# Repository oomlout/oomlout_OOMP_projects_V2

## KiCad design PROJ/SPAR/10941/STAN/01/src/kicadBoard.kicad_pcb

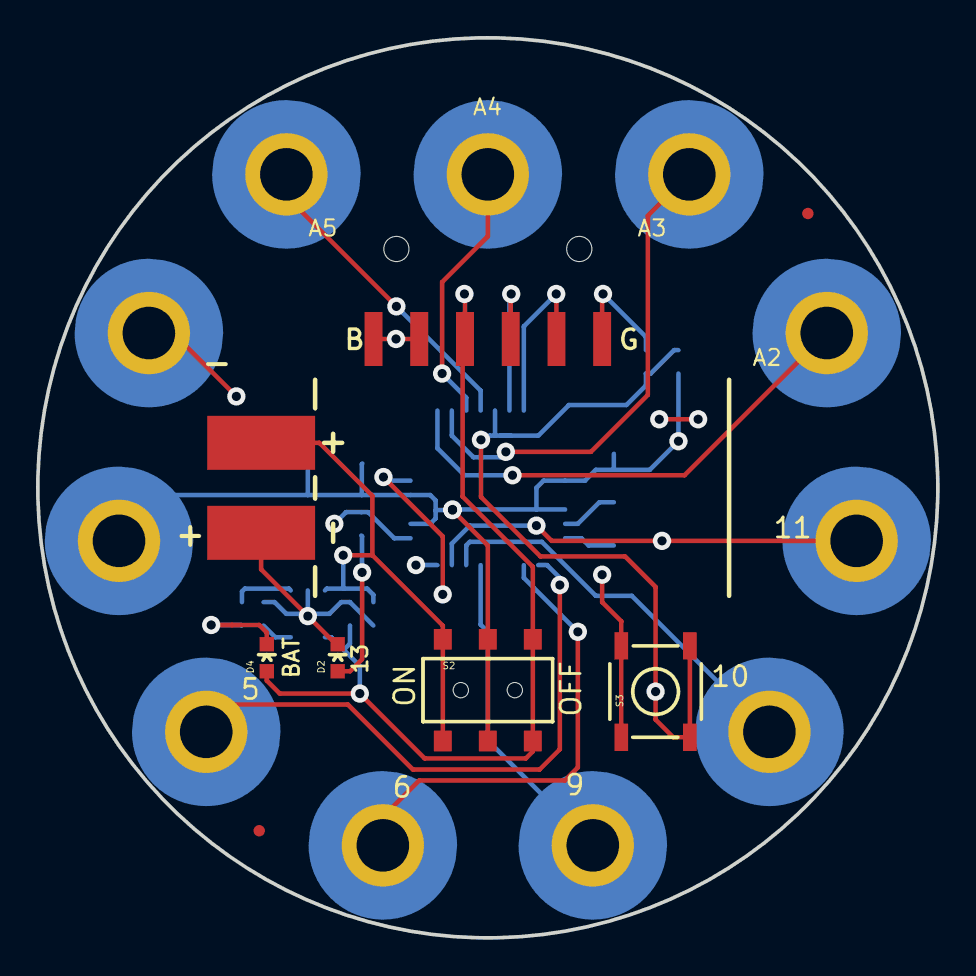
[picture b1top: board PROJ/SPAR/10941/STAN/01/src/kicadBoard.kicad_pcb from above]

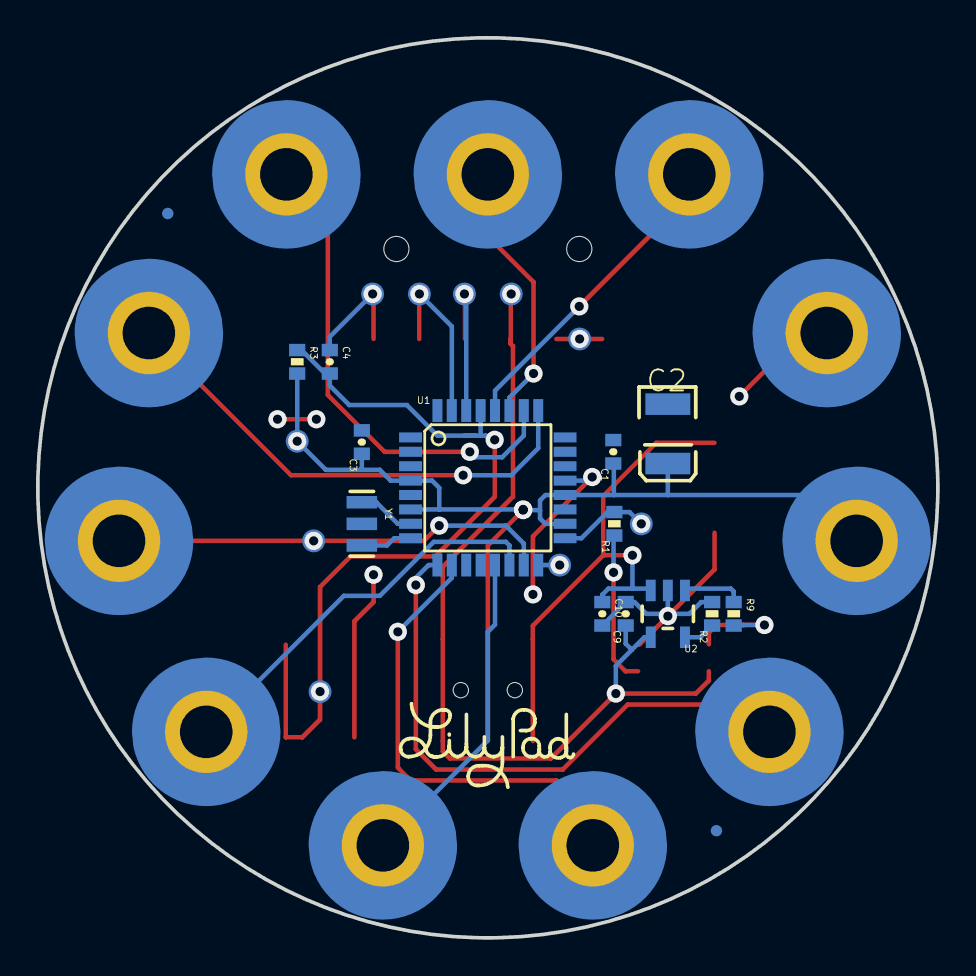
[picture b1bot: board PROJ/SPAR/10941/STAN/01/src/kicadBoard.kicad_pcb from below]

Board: 2 copper layers, 50.0 x 50.0 mm, 45 parts (37 on the bottom side), 25 nets.

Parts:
BAT1: LIPO-110-TABS
C1, C4: 0.1uF; 0402-CAP
C2: 47uF; EIA3528
C3: 1.0uF; 0402-CAP
C9, C10: 4.7uF; 0402-CAP
D2: Status; LED-0603
D4: Yellow; LED-0603
JP1, JP14, JP15, JP16: FIDUCIALUFIDUCIAL; MICRO-FIDUCIAL
JP2: 1X06-SMD
JP3, JP4, JP5, JP6, JP7, JP8, JP9, JP10, JP11, JP12, JP13: M01SNAP-FEMALE_LARGE; SNAP-FEMALE
PP-GND0: PAD.03X.05
PP-MISO0: PAD.03X.05
PP-MOSI0: PAD.03X.05
PP-RST0: PAD.03X.05
PP-SCK0: PAD.03X.05
PP-VCC0: PAD.03X.05
R1, R9: 330; 0402-RES
R2: 10k; 0402-RES
R3: 10K; 0402-RES
S2: On/Off; AYZ0202
S3: Reset; TACTILE_SWITCH_SMD
TP-DTR0: PAD.03X.05
TP-FTDI_VCC0: PAD.03X.05
TP-RX0: PAD.03X.05
TP-TX0: PAD.03X.05
U1: ATMEGA328; TQFP32-08
U2: MCP73831; SOT23-5
U$2: LOGO-LPLP; LOGO-LILYPAD
Y1: 8MHz; RESONATOR-SMD

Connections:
A2: JP3.1, U1.25
A3: JP4.1, U1.26
A4: JP5.1, U1.27
A5: JP6.1, U1.28
D5: JP7.1, U1.9
D6: JP8.1, U1.10
D9: JP9.1, U1.13
D10: JP10.1, U1.14
D11: JP11.1, PP-MOSI0.P$1, U1.15
D12: PP-MISO0.P$1, U1.16
D13: PP-SCK0.P$1, R1.2, U1.17
DTR: C4.1, JP2.1, TP-DTR0.P$1
FTDI_VCC: C9.1, D4.A, JP2.4, S2.3, S2.6, TP-FTDI_VCC0.P$1, U2.4
GND: BAT1.-, C1.2, C2.C, C3.2, C9.2, C10.2, D2.C, JP2.5, JP2.6, JP13.1, PP-GND0.P$1, R2.2, S3.1, U1.3, U1.5, U1.21, U2.2, Y1.2
unnamed: U1.7, Y1.1
unnamed: D2.A, R1.1
unnamed: U1.8, Y1.3
unnamed: D4.C, R9.2
PROG: R2.1, U2.5
RST: C4.2, PP-RST0.P$1, R3.1, S3.3, U1.29
RXI: JP2.3, TP-RX0.P$1, U1.30
STAT: R9.1, U2.1
TXO: JP2.2, TP-TX0.P$1, U1.31
VBATT: BAT1.+, C10.1, S2.1, S2.4, U2.3
VCC: C1.1, C2.A, C3.1, JP12.1, PP-VCC0.P$1, R3.2, S2.2, S2.5, U1.4, U1.6, U1.18, U1.20

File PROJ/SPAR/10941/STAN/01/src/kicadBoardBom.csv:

"Id";"Designator";"Package";"Quantity";"Designation";"Supplier and ref";
1;"JP2";"1X06-SMD";1;"";;;
2;"JP14,JP1,JP16,JP15";"MICRO-FIDUCIAL";4;"FIDUCIALUFIDUCIAL";;;
3;"D2";"LED-0603";1;"Status";;;
4;"BAT1";"LIPO-110-TABS";1;"";;;
5;"S3";"TACTILE_SWITCH_SMD";1;"Reset";;;
6;"D4";"LED-0603";1;"Yellow";;;
7;"S2";"AYZ0202";1;"On/Off";;;
8;"TP-DTR0,TP-FTDI_VCC0,TP-RX0,PP-RST0,PP-MOSI0,PP-SCK0,PP-VCC0,PP-GND0,PP-MISO0,TP-TX0";"PAD.03X.05";10;"";;;
9;"JP6,JP8,JP5,JP3,JP12,JP7,JP9,JP4,JP10,JP13,JP11";"SNAP-FEMALE";11;"M01SNAP-FEMALE_LARGE";;;
10;"C4,C1";"0402-CAP";2;"0.1uF";;;
11;"R1,R9";"0402-RES";2;"330";;;
12;"C10,C9";"0402-CAP";2;"4.7uF";;;
13;"Y1";"RESONATOR-SMD";1;"8MHz";;;
14;"U1";"TQFP32-08";1;"ATMEGA328";;;
15;"U2";"SOT23-5";1;"MCP73831";;;
16;"C3";"0402-CAP";1;"1.0uF";;;
17;"R2";"0402-RES";1;"10k";;;
18;"U$2";"LOGO-LILYPAD";1;"LOGO-LPLP";;;
19;"C2";"EIA3528";1;"47uF";;;
20;"R3";"0402-RES";1;"10K";;;

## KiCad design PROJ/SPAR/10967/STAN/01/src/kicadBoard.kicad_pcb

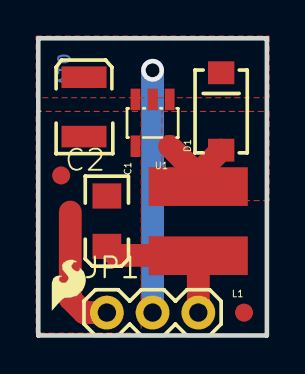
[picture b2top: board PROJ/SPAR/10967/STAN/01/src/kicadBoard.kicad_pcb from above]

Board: 2 copper layers, 12.7 x 16.5 mm, 12 parts (1 on the bottom side), 4 nets.

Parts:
C1: 10uF; EIA3216
C2: 68uF; EIA3528
D1: MBRA140; SMA-DIODE
FID1, FID2: FIDUCIAL1X2; FIDUCIAL-1X2
FRAME1: FRAME-LETTER; CREATIVE_COMMONS
JP1: 1X03
JP2: LOGO-SFESK; SFE-LOGO-FLAME
L1: 47uH; CR54
U1: NCP1402; SOT23-5
U$1: OSHW-LOGOS; OSHW-LOGO-S
U$2: CREATIVE_COMMONS

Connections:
GND: C1.C, C2.C, JP1.1, U1.4
unnamed: D1.A, L1.P$2, U1.5
VIN: C1.A, JP1.3, L1.P$1
VOUT: C2.A, D1.C, JP1.2, U1.1, U1.2

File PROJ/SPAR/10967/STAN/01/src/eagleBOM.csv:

"Part";"Value";"Device";"Package";"Description";"";
"C1";"10uF";"CAP_POL1206";"EIA3216";"Capacitor Polarized";"";
"C2";"68uF";"CAP_POL3528";"EIA3528";"Capacitor Polarized";"";
"D1";"MBRA140";"DIODESMA";"SMA-DIODE";"Diode";"";
"FID1";"FIDUCIAL1X2";"FIDUCIAL1X2";"FIDUCIAL-1X2";"Fiducial Alignment Points";"";
"FID2";"FIDUCIAL1X2";"FIDUCIAL1X2";"FIDUCIAL-1X2";"Fiducial Alignment Points";"";
"FRAME1";"FRAME-LETTER";"FRAME-LETTER";"CREATIVE_COMMONS";"Schematic Frame";"";
"JP1";"";"M03PTH";"1X03";"Header 3";"";
"JP2";"LOGO-SFESK";"LOGO-SFESK";"SFE-LOGO-FLAME";"Spark Fun Electronics PCB Logo";"";
"L1";"47uH";"INDUCTORCR54";"CR54";"Inductors";"";
"U$1";"OSHW-LOGOS";"OSHW-LOGOS";"OSHW-LOGO-S";"Open Source Hardware Logo This logo indicates the piece of hardware it is found on incorporates a OSHW license and/or adheres to the definition of open source hardware found here: http://freedomdefined.org/OSHW";"";
"U$2";"CREATIVE_COMMONS";"CREATIVE_COMMONS";"CREATIVE_COMMONS";"";"";
"U1";"NCP1402";"V_REG_NCP1400SOT23-5";"SOT23-5";"Switching step-up voltage regulator";"";

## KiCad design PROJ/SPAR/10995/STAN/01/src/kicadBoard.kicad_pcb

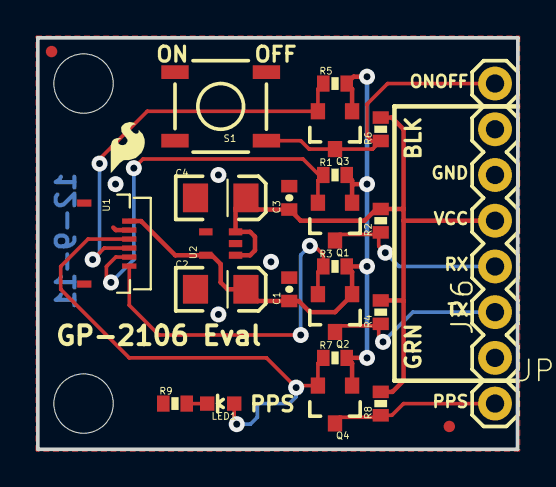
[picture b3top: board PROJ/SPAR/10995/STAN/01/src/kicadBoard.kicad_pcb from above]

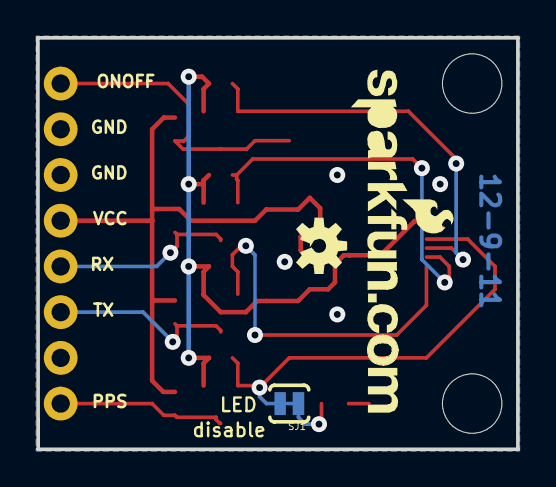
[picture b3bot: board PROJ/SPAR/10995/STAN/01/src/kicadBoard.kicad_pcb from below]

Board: 2 copper layers, 26.7 x 22.9 mm, 33 parts (3 on the bottom side), 13 nets.

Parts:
C1: 1uF; 0402-CAP
C2, C4: 10uF; EIA3216
C3: 0.1uF; 0402-CAP
JP1, JP7: M01PTH; 1X01
JP2, JP3: STAND-OFF
JP4: LOGO-SFESK; SFE-LOGO-FLAME
JP5: LOGO-SFENEW; SFE-NEW-WEBLOGO
JP6: FTDI_BASICPTH; FTDI_BASIC
JP8, JP9: FIDUCIALUFIDUCIAL; MICRO-FIDUCIAL
LED1: red; LED-0603
Q1, Q2, Q3, Q4: MOSFET-NCHANNELSMD; SOT23-3
R1, R2, R3, R4, R5, R6, R7, R8: 10k; 0402-RES
R9: 0.27; 0402-RES
S1: SWITCH-MOMENTARY-2SMD; TACTILE_SWITCH_SMD
SJ1: SOLDERJUMPERTRACE; SJ_2S-TRACE
U1: GP-2106
U2: V_REG_LDOSMD2; SC70
U$7: OSHW-LOGOS; OSHW-LOGO-S
U$8: CREATIVE_COMMONS

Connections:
1.8V: C1.1, C2.A, Q1.1, Q2.1, Q3.1, Q4.1, R1.2, R3.2, R5.2, R7.2, U1.VCC, U2.5
1PPS: JP7.1, Q4.3, R8.1
1PPS_I: Q4.2, R7.1, SJ1.2, U1.1PPS
GND: C1.2, C2.C, C3.2, C4.C, JP6.CTS, JP6.GND, R9.1, S1.3, U1.GND, U2.2
unnamed: LED1.C, R9.2
unnamed: LED1.A, SJ1.1
ONOFF: JP1.1, Q3.3, R6.1, S1.1
ONOFF_I: Q3.2, R5.1, U1.ONOFF
RX: JP6.TXO, Q1.3, R2.1
RX_I: Q1.2, R1.1, U1.RX
TX: JP6.RXI, Q2.3, R4.1
TX_O: Q2.2, R3.1, U1.TX
VCC: C3.1, C4.A, JP6.VCC, R2.2, R4.2, R6.2, R8.2, U2.1, U2.3

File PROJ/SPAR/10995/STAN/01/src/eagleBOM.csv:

"Part";"Value";"Device";"Package";"Description";"";
"C1";"1uF";"CAP0402-CAP";"0402-CAP";"Capacitor";"";
"C2";"10uF";"CAP_POL1206";"EIA3216";"Capacitor Polarized";"";
"C3";"0.1uF";"CAP0402-CAP";"0402-CAP";"Capacitor";"";
"C4";"10uF";"CAP_POL1206";"EIA3216";"Capacitor Polarized";"";
"JP1";"M01PTH";"M01PTH";"1X01";"Header 1";"";
"JP2";"STAND-OFF";"STAND-OFF";"STAND-OFF";"Stand Off";"";
"JP3";"STAND-OFF";"STAND-OFF";"STAND-OFF";"Stand Off";"";
"JP4";"LOGO-SFESK";"LOGO-SFESK";"SFE-LOGO-FLAME";"Spark Fun Electronics PCB Logo";"";
"JP5";"LOGO-SFENEW";"LOGO-SFENEW";"SFE-NEW-WEBLOGO";"Spark Fun Electronics PCB Logo";"";
"JP6";"FTDI_BASICPTH";"FTDI_BASICPTH";"FTDI_BASIC";"FTDI Basic: 3.3V and 5V";"";
"JP7";"M01PTH";"M01PTH";"1X01";"Header 1";"";
"JP8";"FIDUCIALUFIDUCIAL";"FIDUCIALUFIDUCIAL";"MICRO-FIDUCIAL";"Fiducial Alignment Points";"";
"JP9";"FIDUCIALUFIDUCIAL";"FIDUCIALUFIDUCIAL";"MICRO-FIDUCIAL";"Fiducial Alignment Points";"";
"LED1";"red";"LED0603";"LED-0603";"LEDs";"";
"Q1";"MOSFET-NCHANNELSMD";"MOSFET-NCHANNELSMD";"SOT23-3";"";"";
"Q2";"MOSFET-NCHANNELSMD";"MOSFET-NCHANNELSMD";"SOT23-3";"";"";
"Q3";"MOSFET-NCHANNELSMD";"MOSFET-NCHANNELSMD";"SOT23-3";"";"";
"Q4";"MOSFET-NCHANNELSMD";"MOSFET-NCHANNELSMD";"SOT23-3";"";"";
"R1";"10k";"RESISTOR0402-RES";"0402-RES";"Resistor";"";
"R2";"10k";"RESISTOR0402-RES";"0402-RES";"Resistor";"";
"R3";"10k";"RESISTOR0402-RES";"0402-RES";"Resistor";"";
"R4";"10k";"RESISTOR0402-RES";"0402-RES";"Resistor";"";
"R5";"10k";"RESISTOR0402-RES";"0402-RES";"Resistor";"";
"R6";"10k";"RESISTOR0402-RES";"0402-RES";"Resistor";"";
"R7";"10k";"RESISTOR0402-RES";"0402-RES";"Resistor";"";
"R8";"10k";"RESISTOR0402-RES";"0402-RES";"Resistor";"";
"R9";"0.27";"RESISTOR0402-RES";"0402-RES";"Resistor";"";
"S1";"SWITCH-MOMENTARY-2SMD";"SWITCH-MOMENTARY-2SMD";"TACTILE_SWITCH_SMD";"";"";
"SJ1";"SOLDERJUMPERTRACE";"SOLDERJUMPERTRACE";"SJ_2S-TRACE";"Solder Jumper";"";
"U$7";"OSHW-LOGOS";"OSHW-LOGOS";"OSHW-LOGO-S";"Open Source Hardware Logo This logo indicates the piece of hardware it is found on incorporates a OSHW license and/or adheres to the definition of open source hardware found here: http://freedomdefined.org/OSHW";"";
"U$8";"CREATIVE_COMMONS";"CREATIVE_COMMONS";"CREATIVE_COMMONS";"";"";
"U1";"GP-2106";"GP-2106";"GP-2106";"GP-2106 GPS SiRF IV";"";
"U2";"V_REG_LDOSMD2";"V_REG_LDOSMD2";"SC70";"Voltage Regulator LDO";"";

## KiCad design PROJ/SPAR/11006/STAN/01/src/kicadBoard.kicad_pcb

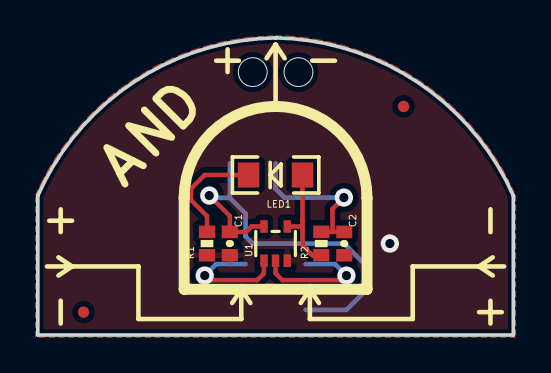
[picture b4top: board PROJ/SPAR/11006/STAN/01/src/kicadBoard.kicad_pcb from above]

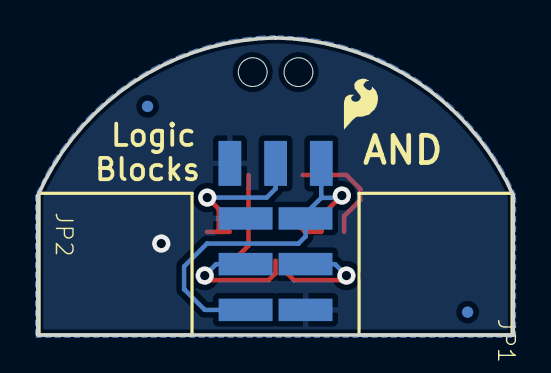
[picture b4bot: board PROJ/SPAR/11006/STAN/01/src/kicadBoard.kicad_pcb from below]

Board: 2 copper layers, 26.4 x 16.5 mm, 14 parts (6 on the bottom side), 7 nets.

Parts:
C1: 0.1uF; 0402-CAP
C2: 1uF; 0402-CAP
JP1, JP2: INPUT; 1X03-SMD-FEMALE
JP4, JP6, JP7, JP8: FIDUCIALUFIDUCIAL; MICRO-FIDUCIAL
JP5: LOGO-SFESK; SFE-LOGO-FLAME
JP9: OUTPUT; 1X03_SMD_RA_MALE_POST
LED1: BLUE; LED-1206
R1: 200; 0402-RES
R2: 499k; 0402-RES
U1: 7408SE; SOT353

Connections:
GND: C1.2, C2.2, JP1.6, JP2.6, JP9.3, R1.1, U1.3
unnamed: JP1.5, U1.1
unnamed: JP2.5, U1.2
unnamed: C2.1, JP9.2, R2.2
unnamed: LED1.A, R2.1, U1.4
unnamed: LED1.C, R1.2
VCC: C1.1, JP1.4, JP2.4, JP9.1, U1.5

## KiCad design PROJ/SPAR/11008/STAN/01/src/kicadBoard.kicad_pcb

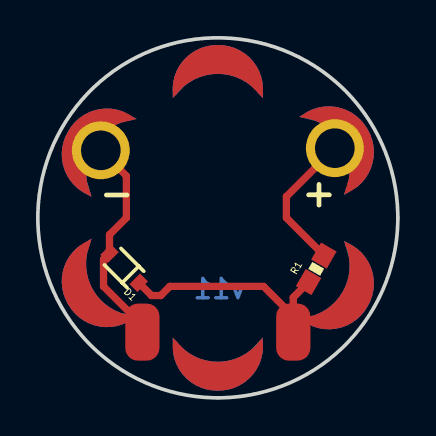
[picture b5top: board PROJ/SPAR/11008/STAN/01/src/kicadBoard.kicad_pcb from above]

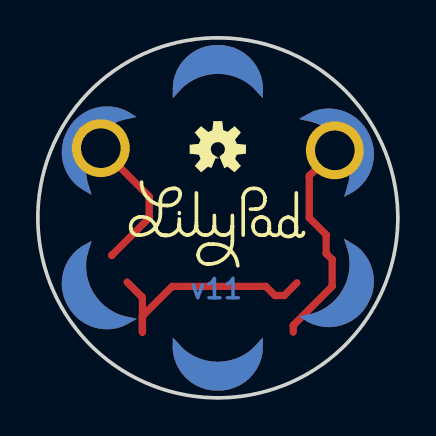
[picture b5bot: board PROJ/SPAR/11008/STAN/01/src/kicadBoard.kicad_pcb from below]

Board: 2 copper layers, 20.0 x 20.0 mm, 12 parts (2 on the bottom side), 3 nets.

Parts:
D1: SOD-323
FRAME1: FRAME-LETTER; CREATIVE_COMMONS
LOGO1: OSHW-LOGOS; OSHW-LOGO-S
M1: MOTORSMD; VIBE-MOTOR-10MM-SMD
R1: 33; 0603-RES
U$2: LOGO-LPLP; LOGO-LILYPAD
VIBE1, VIBE3, VIBE4: SEWTAP-NOHOLE2; PETAL-NOHOLE-2SIDE
VIBE2: SEWTAP-NOHOLEW-MASK; PETAL-NOHOLE-2SIDE-SPECIAL-W-MASK
VIBE+0: SEWTAP6; PETAL-SMALL-2SIDE
VIBE-0: SEWTAP6; PETAL-SMALL-2SIDE

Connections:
5V: R1.2, VIBE+0.1
GND: D1.2, M1.P$2, VIBE-0.1
unnamed: D1.1, M1.P$1, R1.1

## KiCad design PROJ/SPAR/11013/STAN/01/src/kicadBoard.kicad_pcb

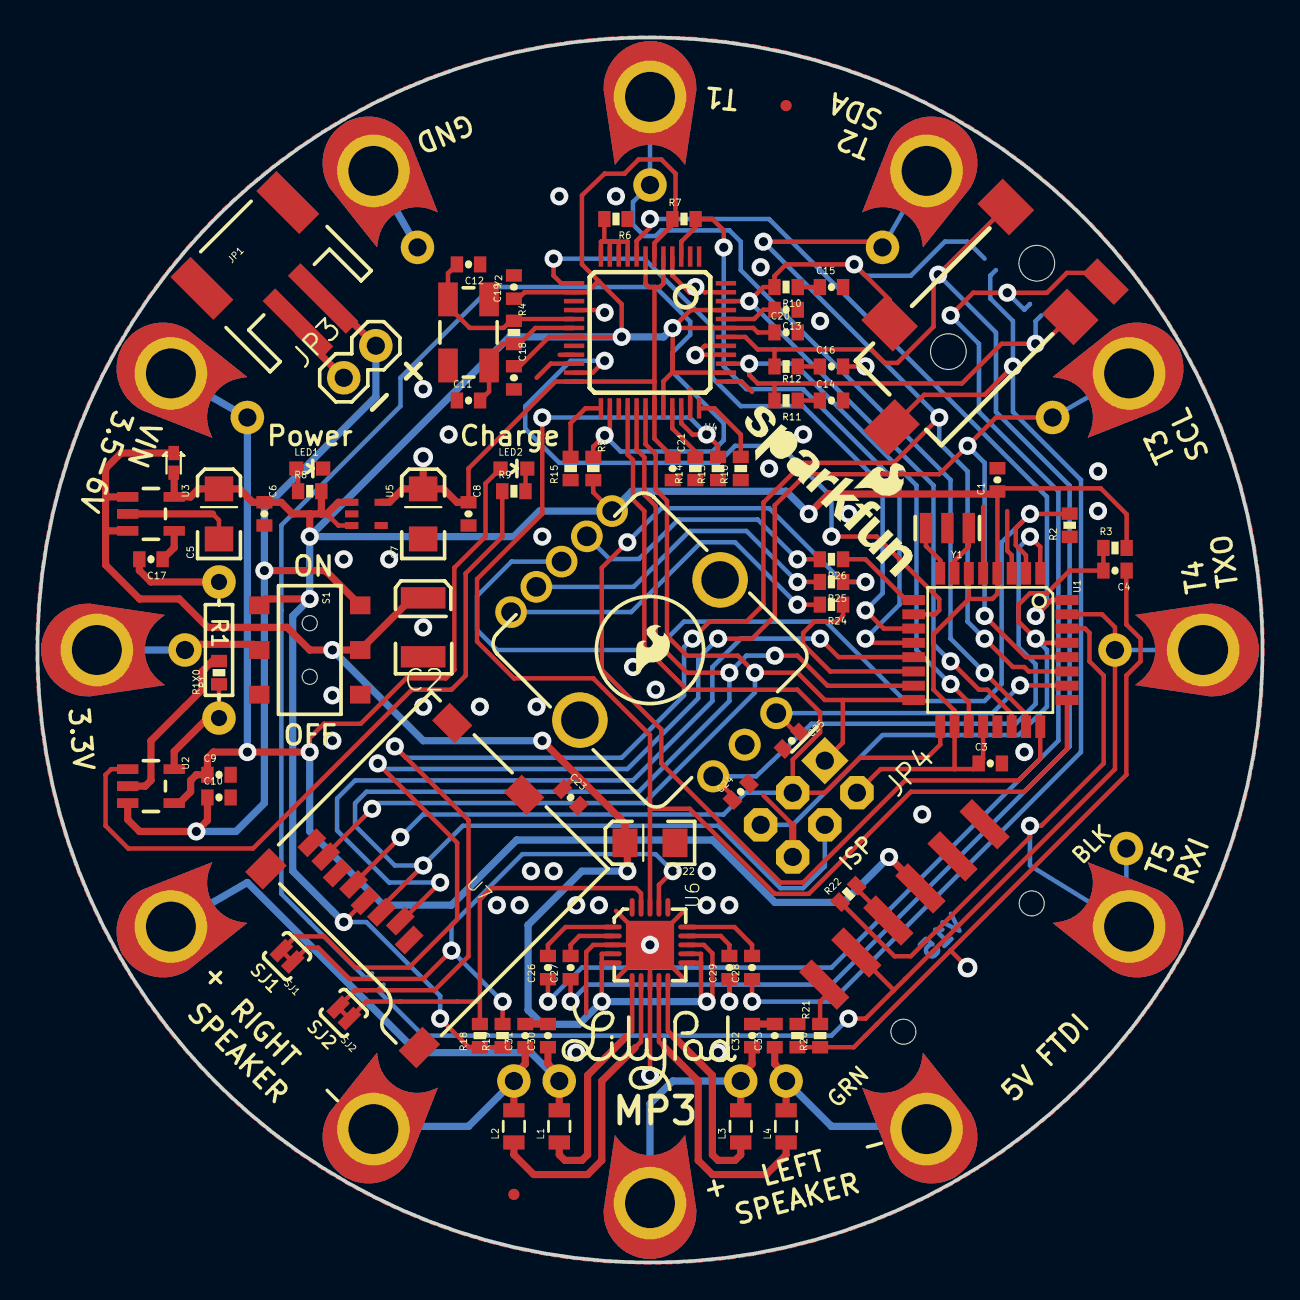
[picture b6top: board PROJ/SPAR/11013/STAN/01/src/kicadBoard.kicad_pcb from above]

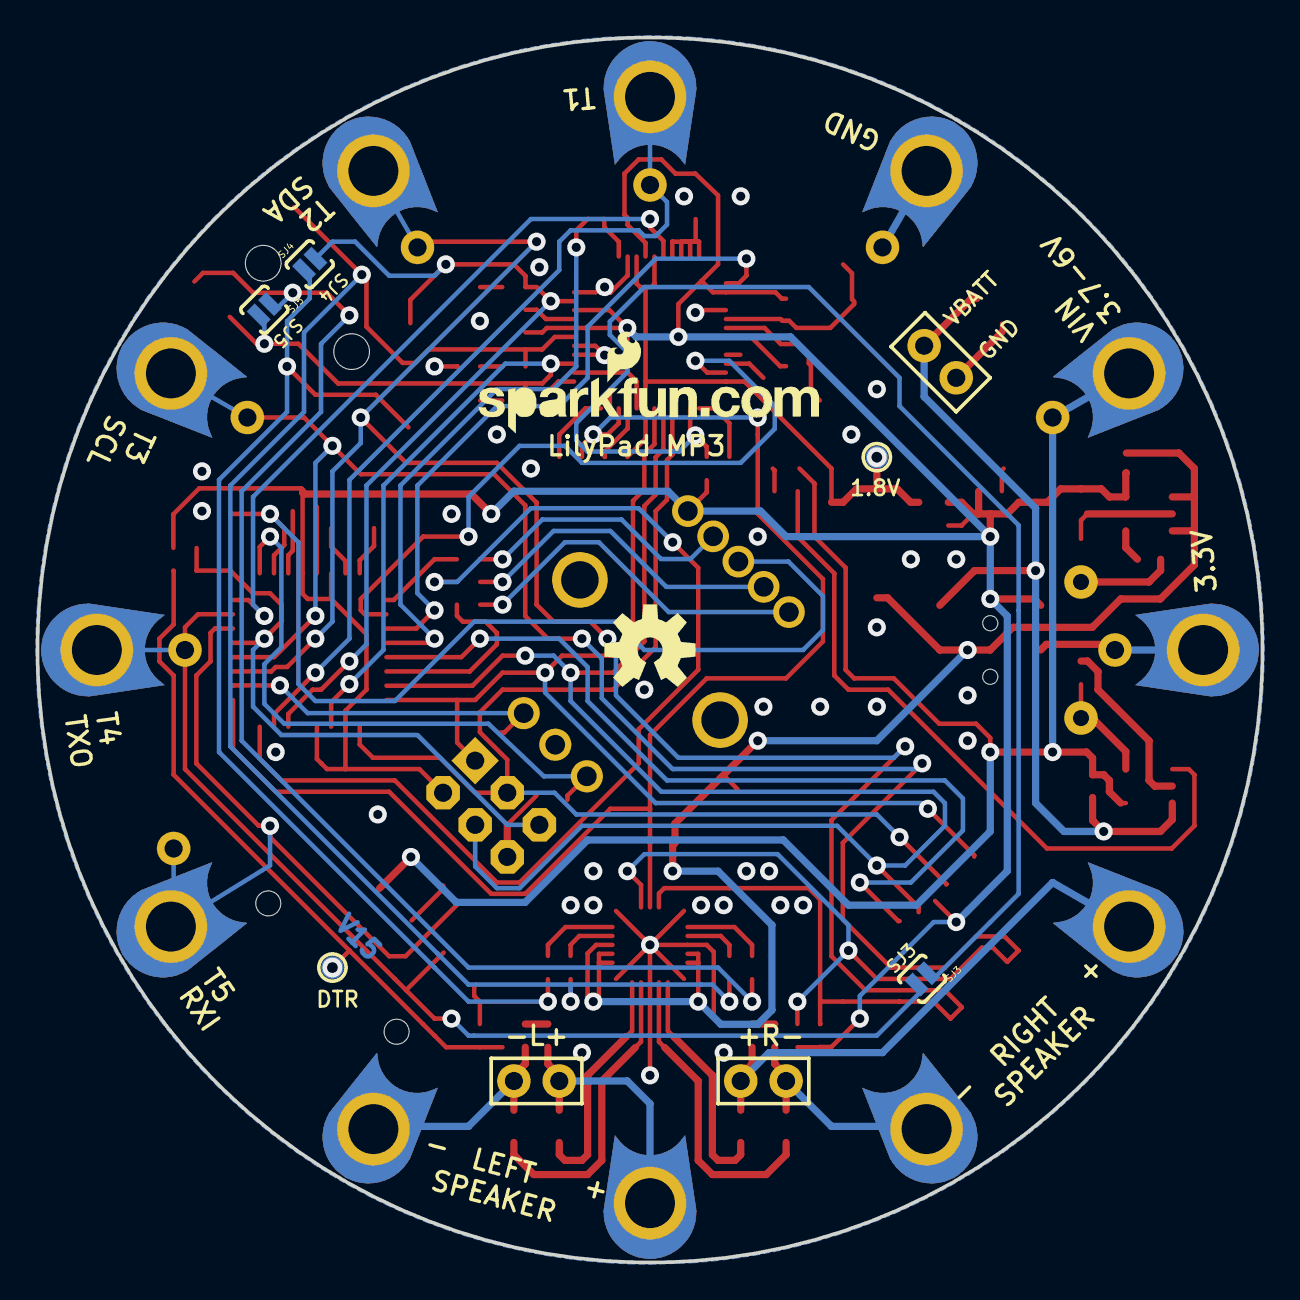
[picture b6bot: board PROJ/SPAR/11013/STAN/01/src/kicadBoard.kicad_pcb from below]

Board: 2 copper layers, 68.6 x 68.6 mm, 121 parts (7 on the bottom side), 69 nets.

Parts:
C1, C4, C6, C8, C18, C19, C20, C21, C23, C24, C25: 0.1uF; 0402-CAP
C2: 47uF; EIA3528
C3, C13, C26, C27, C28, C29: 1uF; 0402-CAP
C5, C7, C22: 10uF; EIA3216
C9, C10: 4.7uF; 0402-CAP
C11, C12: 22pF; 0402-CAP
C14, C15: 10nF; 0402-CAP
C16: 47nF; 0402-CAP
C17: 470pF; 0402-CAP
C30, C31, C32, C33: 1nF; 0402-CAP
D1: SOD-523
JP1: LiPo; JST-2-SMD
JP2: FTDI; 1X06-SMD
JP3: POWER; 1X02
JP4: PROG; 2X3-NS
JP5: HEADPHONE; AUDIO-JACK-3.5MM-SMD
JP6: LOGO-SFENW2; SFE-NEW-WEB
JP7, JP8: FIDUCIALUFIDUCIAL; MICRO-FIDUCIAL
L1, L2, L3, L4: 0805
LED1: RED; LED-0603
LED2: YELLOW; LED-0603
LOGO1, LOGO3: LOGO-SFESK; SFE-LOGO-FLAME
LOGO2: LOGO-SFENEW; SFE-NEW-WEBLOGO
R1, R21: 2K; 0402-RES
R1X0: DNP; AXIAL-0.3
R2, R20: 1K; 0402-RES
R3, R22: 10K; 0402-RES
R4: 1M; 0402-RES
R5, R6, R7, R13, R14, R15, R16: 100k; 0402-RES
R8, R9, R24, R25, R26: 330; 0402-RES
R10, R11: 20; 0402-RES
R12: 10; 0402-RES
R18, R19: 4.7K; 0402-RES
S1: POWER; AYZ0202
S2: EC12PLRGBSDVBF-D; ENCODER_LED_3
SJ1, SJ2, SJ3, SJ4, SJ5: SJ_2S-NO
ST1: TRIG2/SDA; PETAL-LONG-1-2SIDE
ST2: TRIG3/SCL; PETAL-LONG-1-2SIDE
ST3: TRIG4/TXO; PETAL-LONG-1-2SIDE
ST4: TRIG5/RXI; PETAL-LONG-1-2SIDE
ST5: SPKL-; PETAL-LONG-1-2SIDE
ST6: SPKL+; PETAL-LONG-1-2SIDE
ST7: SPKR-; PETAL-LONG-1-2SIDE
ST8: SPKR+; PETAL-LONG-1-2SIDE
ST9: 3.3V; PETAL-LONG-1-2SIDE
ST10: VIN; PETAL-LONG-1-2SIDE
ST11: GND; PETAL-LONG-1-2SIDE
ST12: TRIG1; PETAL-LONG-1-2SIDE
TP1: TRIG1; 1X01NS
TP2: TRIG2/SDA; 1X01NS
TP3: TRIG3/SCL; 1X01NS
TP4: TRIG4/TXO; 1X01NS
TP5: TRIG5/RXI; 1X01NS
TP6: SPKL-; 1X01NS
TP7: SPKL+; 1X01NS
TP8: SPKR-; 1X01NS
TP9: SPKR+; 1X01NS
TP10: 3.3V; 1X01NS
TP11: VIN; 1X01NS
TP12: GND; 1X01NS
TP13: DTR; PAD.03X.05
TP14: 1.8V; PAD.03X.05
U1: ATMEGA328; TQFP32-08
U2: MCP73831; SOT23-5
U3: MIC5219 3.3V; SOT23-5
U4: VS1053; LQFP-48
U5: SP6214 1.8V; SC70
U6: TPA2016D2RTJ; QFN-20-0.5MM
U7: USD-SOCKET; MICRO-SD-SOCKET-PP
U$1: LOGO-LPLP; LOGO-LILYPAD
U$4: OSHW-LOGOM; OSHW-LOGO-M
U$12: CREATIVE_COMMONS
Y1: 8MHz; RESONATOR-SMD
Y2: 12.288MHz; CRYSTAL-SMD-5X3

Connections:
1.8V: C7.A, C8.1, C21.1, TP14.P$1, U4.5, U4.7, U4.24, U4.31, U5.5
3.3V: C1.1, C3.1, C5.A, C6.1, C18.1, C19.1, C20.1, D1.A, JP4.2, R3.2, R5.2, R7.1, R8.2, R18.1, R19.1, S1.4, S2.5, U1.4, U1.6, U1.18, U1.20, U3.5, U4.6, U4.14, U4.19, U4.32, U4.38, U4.43, U4.45, U5.1, U5.3, U7.4
3.3V-TAP: S1.5, ST9.1, TP10.1
AMP-L: C28.1, JP5.TSH, SJ4.1
AMP-LX: C26.2, U6.1
AMP-R: C26.1, JP5.RSH, SJ5.1
AMP-RX: C28.2, U6.15
DTR: C4.1, R20.1, R21.2, TP13.P$1
EN-GPIO1: R13.2, U1.25, U4.34, U6.18
FTDI-DTR: JP2.1, R20.2
FTDI-RXI: JP2.3, R22.2
G1: R6.2, U4.9, U4.10, U4.11, U4.12
G2: R15.2, U4.25
GBUF: C27.1, C29.1, JP5.SLEEVE, R12.2, U4.42
GBUFLX: C27.2, U6.2
GBUFRX: C29.2, U6.14
GND: C1.2, C2.C, C3.2, C5.C, C6.2, C7.C, C8.2, C9.2, C10.2, C11.1, C12.1, C13.1, C14.2, C15.2, C16.2, C17.2, C18.2, C19.2, C20.2, C21.2, C22.C, C23.2, C24.2, C25.2, C30.2, C31.2, C32.2, C33.2, JP1.1, JP2.5, JP2.6, JP3.1, JP4.6, LED1.C, R1.2, R1X0.P$2, R2.1, R6.1, R13.1, R14.1, R15.1, R16.1, R21.1, S2.C, ST11.1, TP12.1, U1.3, U1.5, U1.21, U2.2, U3.2, U4.4, U4.16, U4.20, U4.21, U4.22, U4.35, U4.37, U4.40, U4.41, U4.47, U5.2, U6.3, U6.8, U6.PAD, U7.6, U7.CD1, U7.CD2, U7.GND1, U7.GND3, Y1.2
GPIO0: R14.2, U4.33
LEFT: JP5.TIP, R10.2, SJ4.2, U1.22, U4.46
MISO: JP4.1, U1.16, U4.30, U7.7
MOSI: JP4.4, U1.15, U4.29, U7.3
MP3-CS: U1.10, U4.23
MP3-DCS: U1.11, U4.13
MP3-DREQ: U1.32, U4.8
MP3-MIDI-RX: R5.1, SJ3.1, U4.26
MP3-RST: R7.2, U1.12, U4.3
unnamed: U1.7, Y1.1
unnamed: U1.8, Y1.3
unnamed: C13.2, U4.44
unnamed: C16.1, R12.1
unnamed: LED1.A, R8.1
unnamed: C15.1, R10.1
unnamed: LED2.C, R9.2
unnamed: C11.2, R4.2, U4.18, Y2.3
unnamed: C12.2, R4.1, U4.17, Y2.1
unnamed: C14.1, R11.1
unnamed: R24.2, S2.1
unnamed: R25.2, S2.2
unnamed: R26.2, S2.4
unnamed: L1.1, U6.6
unnamed: L2.1, U6.7
unnamed: L3.1, U6.10
unnamed: L4.1, U6.9
unnamed: C17.1, U3.4
unnamed: R16.2, U4.36
PROG: R1.1, R1X0.P$1, U2.5
RIGHT: JP5.RING, R11.2, SJ5.2, U1.19, U4.39
ROT-A: C24.1, S2.A, U1.1
ROT-B: C25.1, S2.B, U1.26
ROT-LEDB: R26.1, U1.9
ROT-LEDG: R25.1, U1.24
ROT-LEDR: R24.1, U1.14
ROT-SW: R2.2, S2.3, U1.2
RST: C4.2, JP4.5, R3.1, U1.29
SCK: JP4.3, U1.17, U4.28, U7.5
SD-CS: U1.13, U7.2
SPKL+: C32.1, L3.2, ST6.1, TP7.1
SPKL-: C33.1, L4.2, ST5.1, TP6.1
SPKR+: C30.1, L1.2, ST8.1, TP9.1
SPKR-: C31.1, L2.2, ST7.1, TP8.1
STAT: R9.1, U2.1
TRIG1: ST12.1, TP1.1, U1.23
TRIG2/SDA: R18.2, SJ2.1, SJ2.2, ST1.1, TP2.1, U1.27, U6.19
TRIG3/SCL: R19.2, SJ1.1, SJ1.2, ST2.1, TP3.1, U1.28, U6.17
TRIG4/TXO: JP2.2, SJ3.2, ST3.1, TP4.1, U1.31
TRIG5/RXI: R22.1, ST4.1, TP5.1, U1.30
VBATT: C10.1, JP1.2, JP3.2, S1.1, U2.3
VBATT_SW: C2.A, C22.A, C23.1, D1.C, S1.2, U3.1, U3.3, U6.4, U6.5, U6.11, U6.12, U6.13
VIN: C9.1, JP2.4, LED2.A, ST10.1, TP11.1, U2.4

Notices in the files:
parts and their libraries:
HTTP://CREATIVECOMMONS.ORG/LICENSES/BY-SA/3.0
RELEASED UNDER THE CREATIVE COMMONS ATTRIBUTION SHARE-ALIKE 3.0 LICENSE
HTTPS://CREATIVECOMMONS.ORG/LICENSES/BY-SA/4.0
RELEASED UNDER THE CREATIVE COMMONS ATTRIBUTION SHARE-ALIKE 4.0 LICENSE
